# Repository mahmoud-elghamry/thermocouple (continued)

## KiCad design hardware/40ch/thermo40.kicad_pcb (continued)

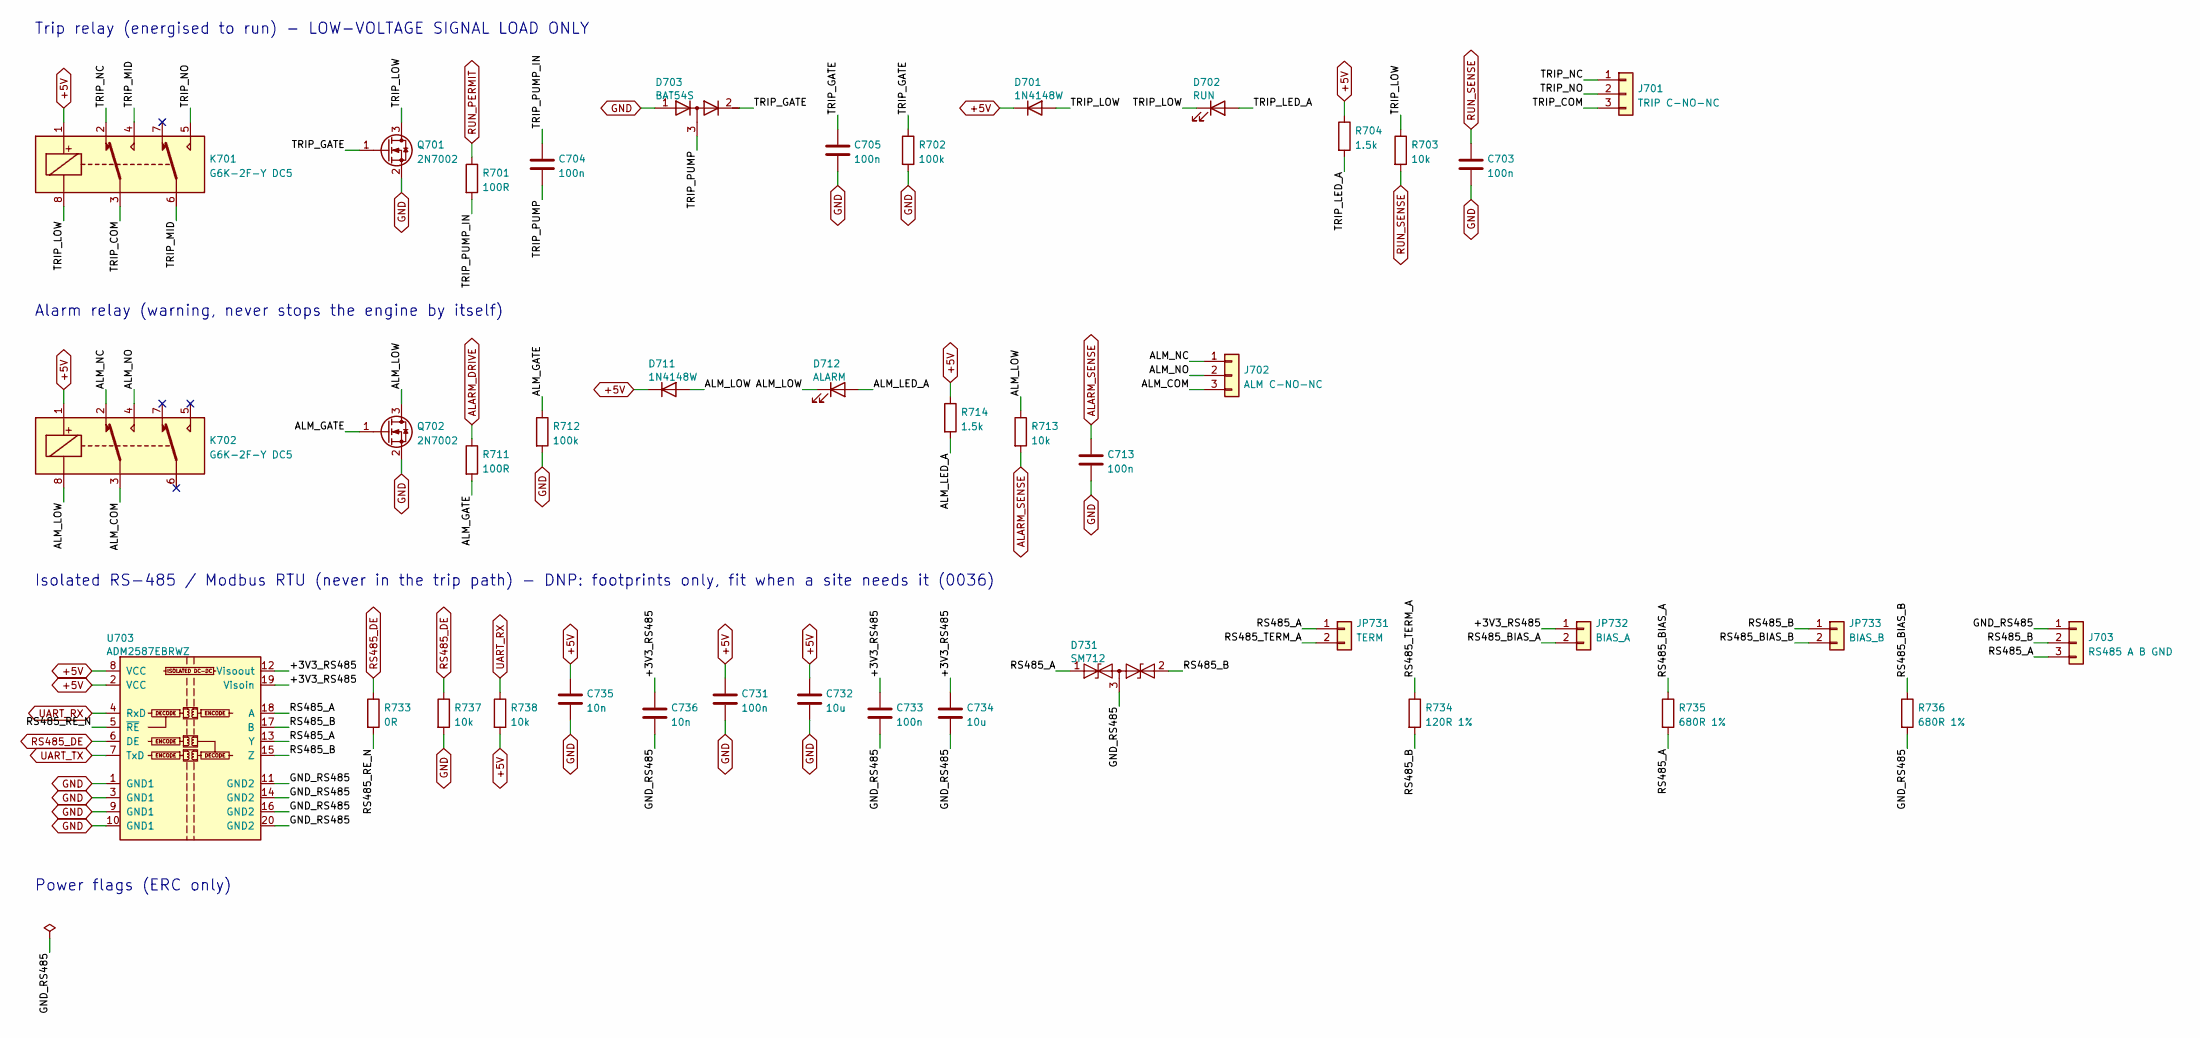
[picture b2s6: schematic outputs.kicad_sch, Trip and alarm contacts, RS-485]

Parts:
C703, C704, C705, C713, C731, C733: 100n; C_0805_2012Metric; MPN CC0805KRX7R9BB104; LCSC C49678
C732, C734: 10u; C_0805_2012Metric; MPN CL21B106KOQNNNE; LCSC C95841
C735, C736: 10n; C_0805_2012Metric; MPN CL21B103KBANNNC; LCSC C1710
D701, D711: 1N4148W; D_SOD-123; MPN 1N4148W-7-F; LCSC C83528
D702: RUN; LED_D3.0mm; MPN 3A4GUD; LCSC C52034646
D703: BAT54S; SOT-23; MPN BAT54S,215; LCSC C47546
D712: ALARM; LED_D3.0mm; MPN 204-10SURD/S530-A3-L; LCSC C99771
D731: SM712; SOT-23; MPN SM712.TCT; LCSC C12067
J701: TRIP C-NO-NC; TerminalBlock_Phoenix_MKDS-1,5-3_1x03_P5.00mm_Horizontal; MPN WJ128V-5.0-3P; LCSC C8270
J702: ALM C-NO-NC; TerminalBlock_Phoenix_MKDS-1,5-3_1x03_P5.00mm_Horizontal; MPN WJ128V-5.0-3P; LCSC C8270
J703: RS485 A B GND; TerminalBlock_Phoenix_MKDS-1,5-3_1x03_P5.00mm_Horizontal; MPN WJ128V-5.0-3P; LCSC C8270
JP731: TERM; PinHeader_1x02_P2.54mm_Vertical; MPN PZ254V-11-02P; LCSC C492401
JP732: BIAS_A; PinHeader_1x02_P2.54mm_Vertical; MPN PZ254V-11-02P; LCSC C492401
JP733: BIAS_B; PinHeader_1x02_P2.54mm_Vertical; MPN PZ254V-11-02P; LCSC C492401
K701, K702: G6K-2F-Y DC5; Relay_DPDT_Omron_G6K-2F-Y; MPN G6K-2F-Y DC5; LCSC C2982926
Q701, Q702: 2N7002; SOT-23; MPN 2N7002; LCSC C8545
R701, R711: 100R; R_0805_2012Metric; MPN 0805W8F1000T5E; LCSC C17408
R702, R712: 100k; R_0805_2012Metric; MPN 0805W8F1003T5E; LCSC C149504
R703, R713, R737, R738: 10k; R_0805_2012Metric; MPN 0805W8F1002T5E; LCSC C17414
R704, R714: 1.5k; R_0805_2012Metric; MPN 0805W8F1501T5E; LCSC C4310
R733: 0R; R_0805_2012Metric; MPN 0805W8F0000T5E; LCSC C17477
R734: 120R 1%; R_0805_2012Metric; MPN 0805W8F1200T5E; LCSC C17437
R735, R736: 680R 1%; R_0805_2012Metric; MPN 0805W8F6800T5E; LCSC C17798
U703: ADM2587EBRWZ; SOIC-20W_7.5x12.8mm_P1.27mm; MPN ADM2587EBRWZ-REEL7; LCSC C12081

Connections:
+5V: C731.1, C732.1, C735.1, D701.1 (K), D711.1 (K), K701.1, K702.1, R704.1, R714.1, R738.2, U703.2 (VCC), U703.8 (VCC); also elsewhere on the board
/OUTPUTS/+3V3_RS485: C733.1, C734.1, C736.1, JP732.1, U703.12 (Visoout), U703.19 (Visoin)
/OUTPUTS/ALM_COM: J702.3, K702.3
/OUTPUTS/ALM_GATE: Q702.1 (G), R711.2, R712.1
/OUTPUTS/ALM_LED_A: D712.2 (A), R714.2
/OUTPUTS/ALM_LOW: D711.2 (A), D712.1 (K), K702.8, Q702.3 (D), R713.1
/OUTPUTS/ALM_NC: J702.1, K702.2
/OUTPUTS/ALM_NO: J702.2, K702.4
/OUTPUTS/GND_RS485: C733.2, C734.2, C736.2, D731.3 (common), J703.1, R736.2, U703.11 (GND2), U703.14 (GND2), U703.16 (GND2), U703.20 (GND2)
/OUTPUTS/RS485_A: D731.1 (A1), J703.3, JP731.1, R735.2, U703.13 (Y), U703.18 (A)
/OUTPUTS/RS485_B: D731.2 (A2), J703.2, JP733.1, R734.2, U703.15 (Z), U703.17 (B)
/OUTPUTS/RS485_BIAS_A: JP732.2, R735.1
/OUTPUTS/RS485_BIAS_B: JP733.2, R736.1
/OUTPUTS/RS485_RE_N: R733.2, U703.5 (~RE)
/OUTPUTS/RS485_TERM_A: JP731.2, R734.1
/OUTPUTS/TRIP_COM: J701.3, K701.3
/OUTPUTS/TRIP_GATE: C705.1, D703.2 (K), Q701.1 (G), R702.1
/OUTPUTS/TRIP_LED_A: D702.2 (A), R704.2
/OUTPUTS/TRIP_LOW: D701.2 (A), D702.1 (K), K701.8, Q701.3 (D), R703.1
/OUTPUTS/TRIP_MID: K701.4, K701.6
/OUTPUTS/TRIP_NC: J701.1, K701.2
/OUTPUTS/TRIP_NO: J701.2, K701.5
/OUTPUTS/TRIP_PUMP: C704.2, D703.3 (common)
/OUTPUTS/TRIP_PUMP_IN: C704.1, R701.2
ALARM_DRIVE: R711.1; also elsewhere on the board
ALARM_SENSE: C713.1, R713.2; also elsewhere on the board
GND: C703.2, C705.2, C713.2, C731.2, C732.2, C735.2, D703.1 (A), Q701.2 (S), Q702.2 (S), R702.2, R712.2, R737.2, U703.1 (GND1), U703.3 (GND1), U703.9 (GND1), U703.10 (GND1); also elsewhere on the board
RS485_DE: R733.1, R737.1, U703.6 (DE); also elsewhere on the board
RUN_PERMIT: R701.1; also elsewhere on the board
RUN_SENSE: C703.1, R703.2; also elsewhere on the board
UART_RX: R738.1, U703.4 (RxD); also elsewhere on the board
UART_TX: U703.7 (TxD); also elsewhere on the board

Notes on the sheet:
Trip relay (energised to run) - LOW-VOLTAGE SIGNAL LOAD ONLY
Alarm relay (warning, never stops the engine by itself)
Isolated RS-485 / Modbus RTU (never in the trip path) - DNP: footprints only, fit when a site needs it (0036)
Power flags (ERC only)

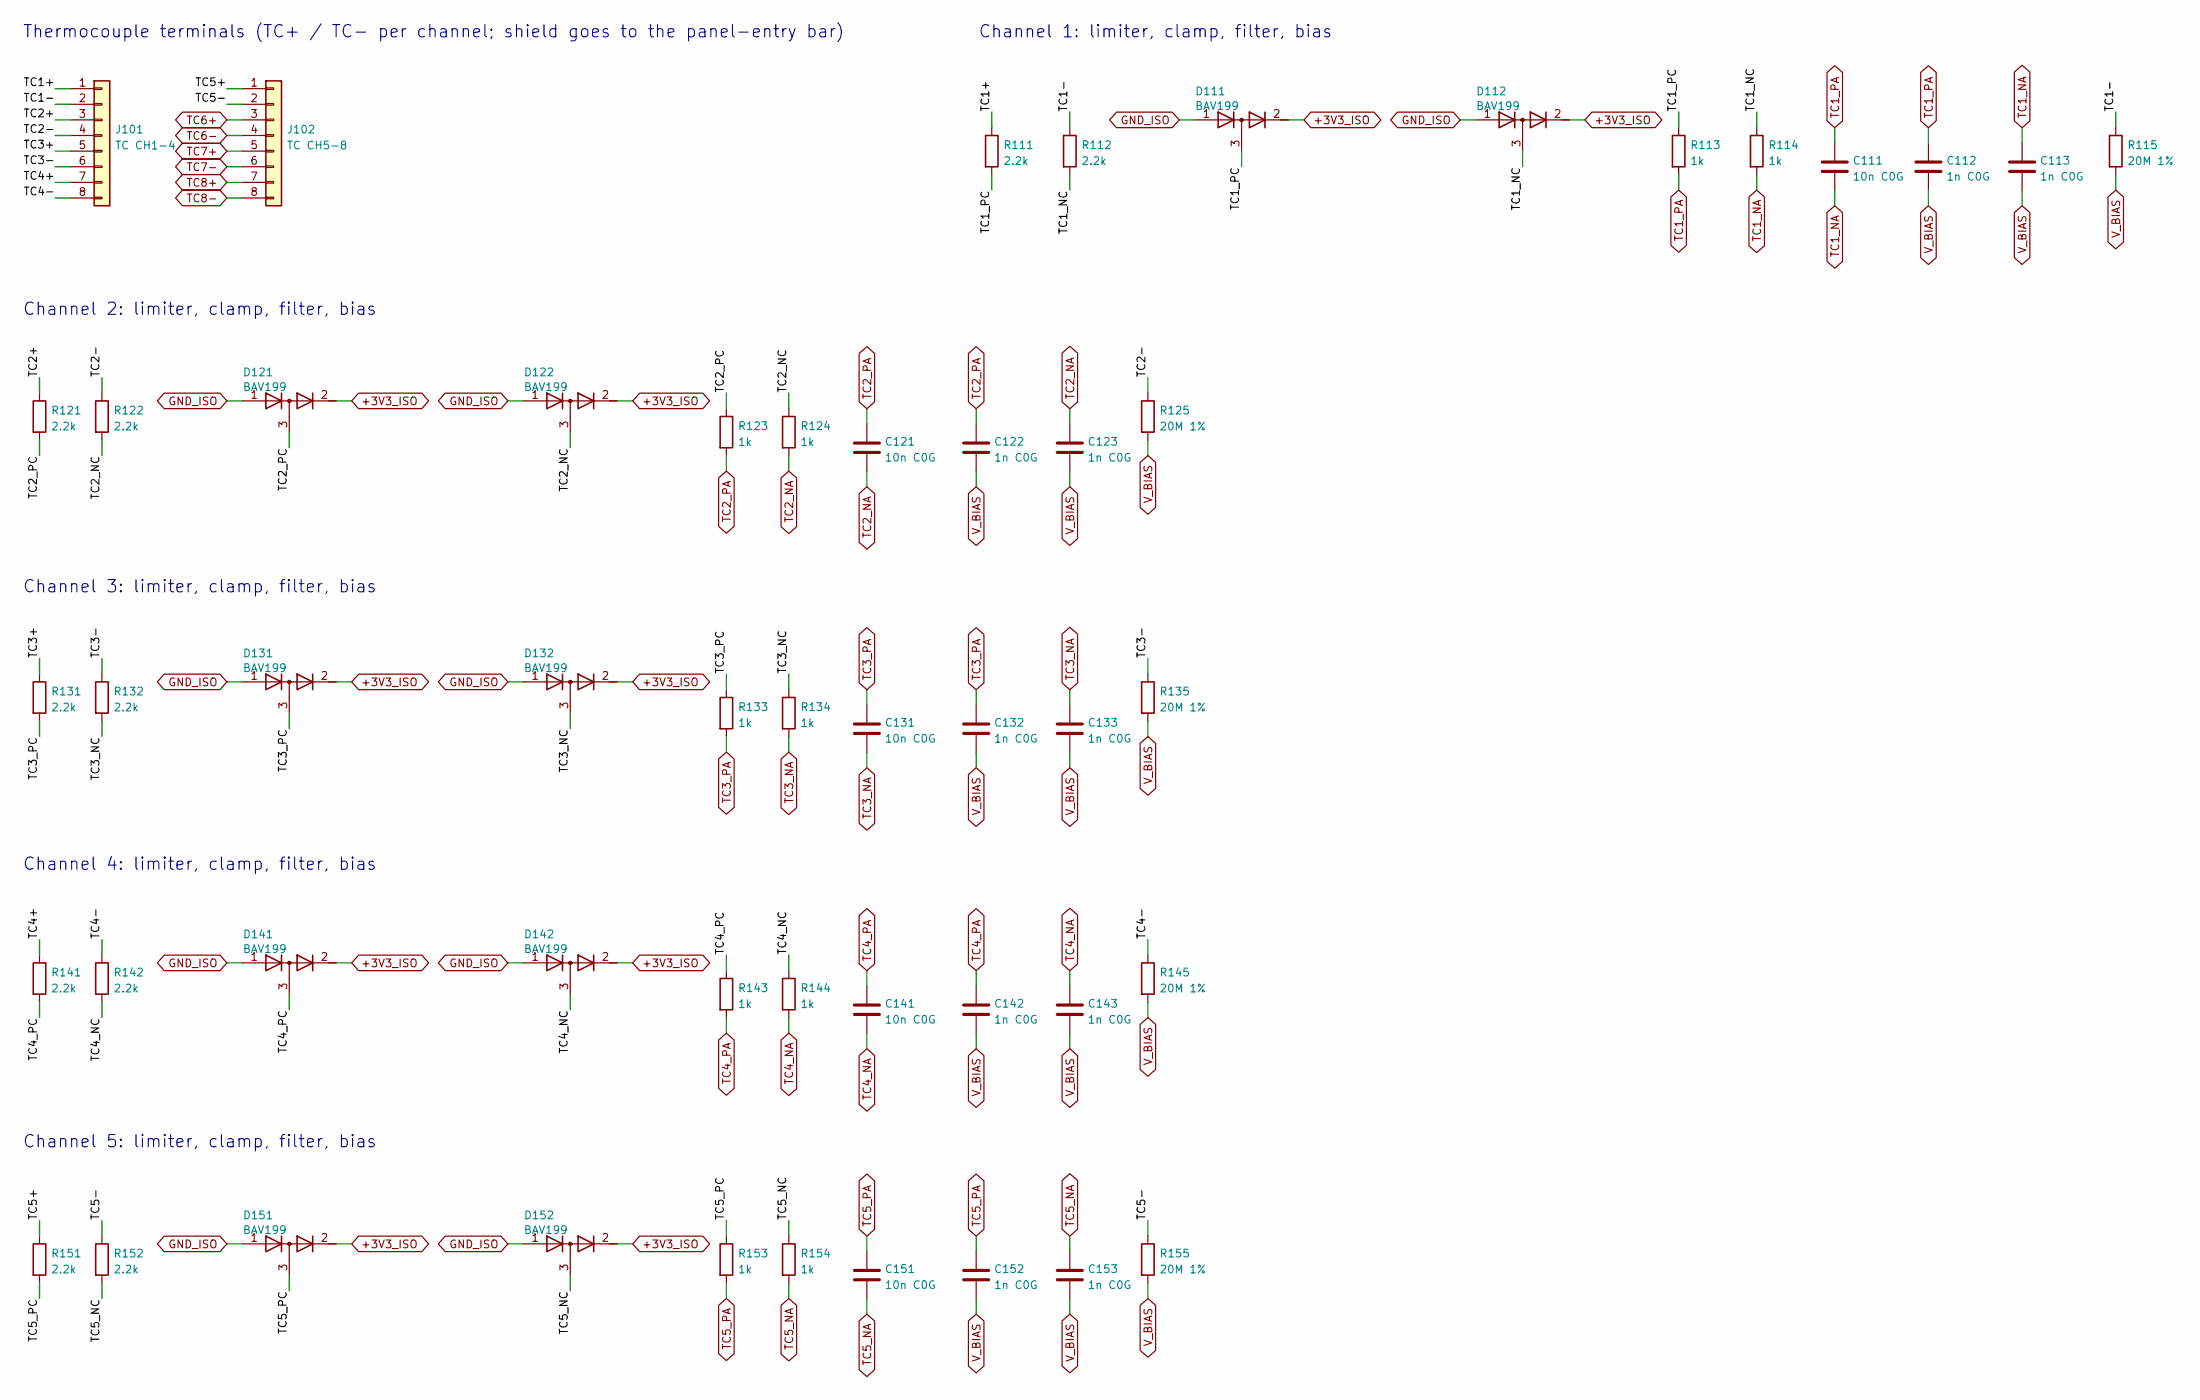
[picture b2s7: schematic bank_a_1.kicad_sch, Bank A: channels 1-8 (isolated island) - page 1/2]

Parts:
C111, C121, C131, C141, C151: 10n C0G; C_0805_2012Metric; MPN GRM2195C1H103JA01D; LCSC C97905
C112, C113, C122, C123, C132, C133, C142, C143, C152, C153: 1n C0G; C_0805_2012Metric; MPN CL21C102JBCNNNC; LCSC C1791
D111, D112, D121, D122, D131, D132, D141, D142, D151, D152: BAV199; SOT-23; MPN BAV199,215; LCSC C40919
J101: TC CH1-4; PhoenixContact_MC_1,5_8-G-3.81_1x08_P3.81mm_Horizontal; MPN WJ15EDGRC-3.81-8P; LCSC C14235
J102: TC CH5-8; PhoenixContact_MC_1,5_8-G-3.81_1x08_P3.81mm_Horizontal; MPN WJ15EDGRC-3.81-8P; LCSC C14235
R111, R112, R121, R122, R131, R132, R141, R142, R151, R152: 2.2k; R_0805_2012Metric; MPN 0805W8F2201T5E; LCSC C17520
R113, R114, R123, R124, R133, R134, R143, R144, R153, R154: 1k; R_0805_2012Metric; MPN 0805W8F1001T5E; LCSC C17513
R115, R125, R135, R145, R155: 20M 1%; R_1206_3216Metric; MPN FRG1206F2005TS; LCSC C3000606

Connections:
+3V3_ISO: D111.2 (K), D112.2 (K), D121.2 (K), D122.2 (K), D131.2 (K), D132.2 (K), D141.2 (K), D142.2 (K), D151.2 (K), D152.2 (K); also elsewhere on the board
/BANK_A_1/TC1+: J101.1, R111.1
/BANK_A_1/TC1-: J101.2, R112.1, R115.1
/BANK_A_1/TC1_NC: D112.3 (common), R112.2, R114.1
/BANK_A_1/TC1_PC: D111.3 (common), R111.2, R113.1
/BANK_A_1/TC2+: J101.3, R121.1
/BANK_A_1/TC2-: J101.4, R122.1, R125.1
/BANK_A_1/TC2_NC: D122.3 (common), R122.2, R124.1
/BANK_A_1/TC2_PC: D121.3 (common), R121.2, R123.1
/BANK_A_1/TC3+: J101.5, R131.1
/BANK_A_1/TC3-: J101.6, R132.1, R135.1
/BANK_A_1/TC3_NC: D132.3 (common), R132.2, R134.1
/BANK_A_1/TC3_PC: D131.3 (common), R131.2, R133.1
/BANK_A_1/TC4+: J101.7, R141.1
/BANK_A_1/TC4-: J101.8, R142.1, R145.1
/BANK_A_1/TC4_NC: D142.3 (common), R142.2, R144.1
/BANK_A_1/TC4_PC: D141.3 (common), R141.2, R143.1
/BANK_A_1/TC5+: J102.1, R151.1
/BANK_A_1/TC5-: J102.2, R152.1, R155.1
/BANK_A_1/TC5_NC: D152.3 (common), R152.2, R154.1
/BANK_A_1/TC5_PC: D151.3 (common), R151.2, R153.1
GND_ISO: D111.1 (A), D112.1 (A), D121.1 (A), D122.1 (A), D131.1 (A), D132.1 (A), D141.1 (A), D142.1 (A), D151.1 (A), D152.1 (A); also elsewhere on the board
TC1_NA: C111.2, C113.1, R114.2; also elsewhere on the board
TC1_PA: C111.1, C112.1, R113.2; also elsewhere on the board
TC2_NA: C121.2, C123.1, R124.2; also elsewhere on the board
TC2_PA: C121.1, C122.1, R123.2; also elsewhere on the board
TC3_NA: C131.2, C133.1, R134.2; also elsewhere on the board
TC3_PA: C131.1, C132.1, R133.2; also elsewhere on the board
TC4_NA: C141.2, C143.1, R144.2; also elsewhere on the board
TC4_PA: C141.1, C142.1, R143.2; also elsewhere on the board
TC5_NA: C151.2, C153.1, R154.2; also elsewhere on the board
TC5_PA: C151.1, C152.1, R153.2; also elsewhere on the board
TC6+: J102.3; also elsewhere on the board
TC6-: J102.4; also elsewhere on the board
TC7+: J102.5; also elsewhere on the board
TC7-: J102.6; also elsewhere on the board
TC8+: J102.7; also elsewhere on the board
TC8-: J102.8; also elsewhere on the board
V_BIAS: C112.2, C113.2, C122.2, C123.2, C132.2, C133.2, C142.2, C143.2, C152.2, C153.2, R115.2, R125.2, R135.2, R145.2, R155.2; also elsewhere on the board

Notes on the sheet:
Thermocouple terminals (TC+ / TC- per channel; shield goes to the panel-entry bar)
Channel 1: limiter, clamp, filter, bias
Channel 2: limiter, clamp, filter, bias
Channel 3: limiter, clamp, filter, bias
Channel 4: limiter, clamp, filter, bias
Channel 5: limiter, clamp, filter, bias

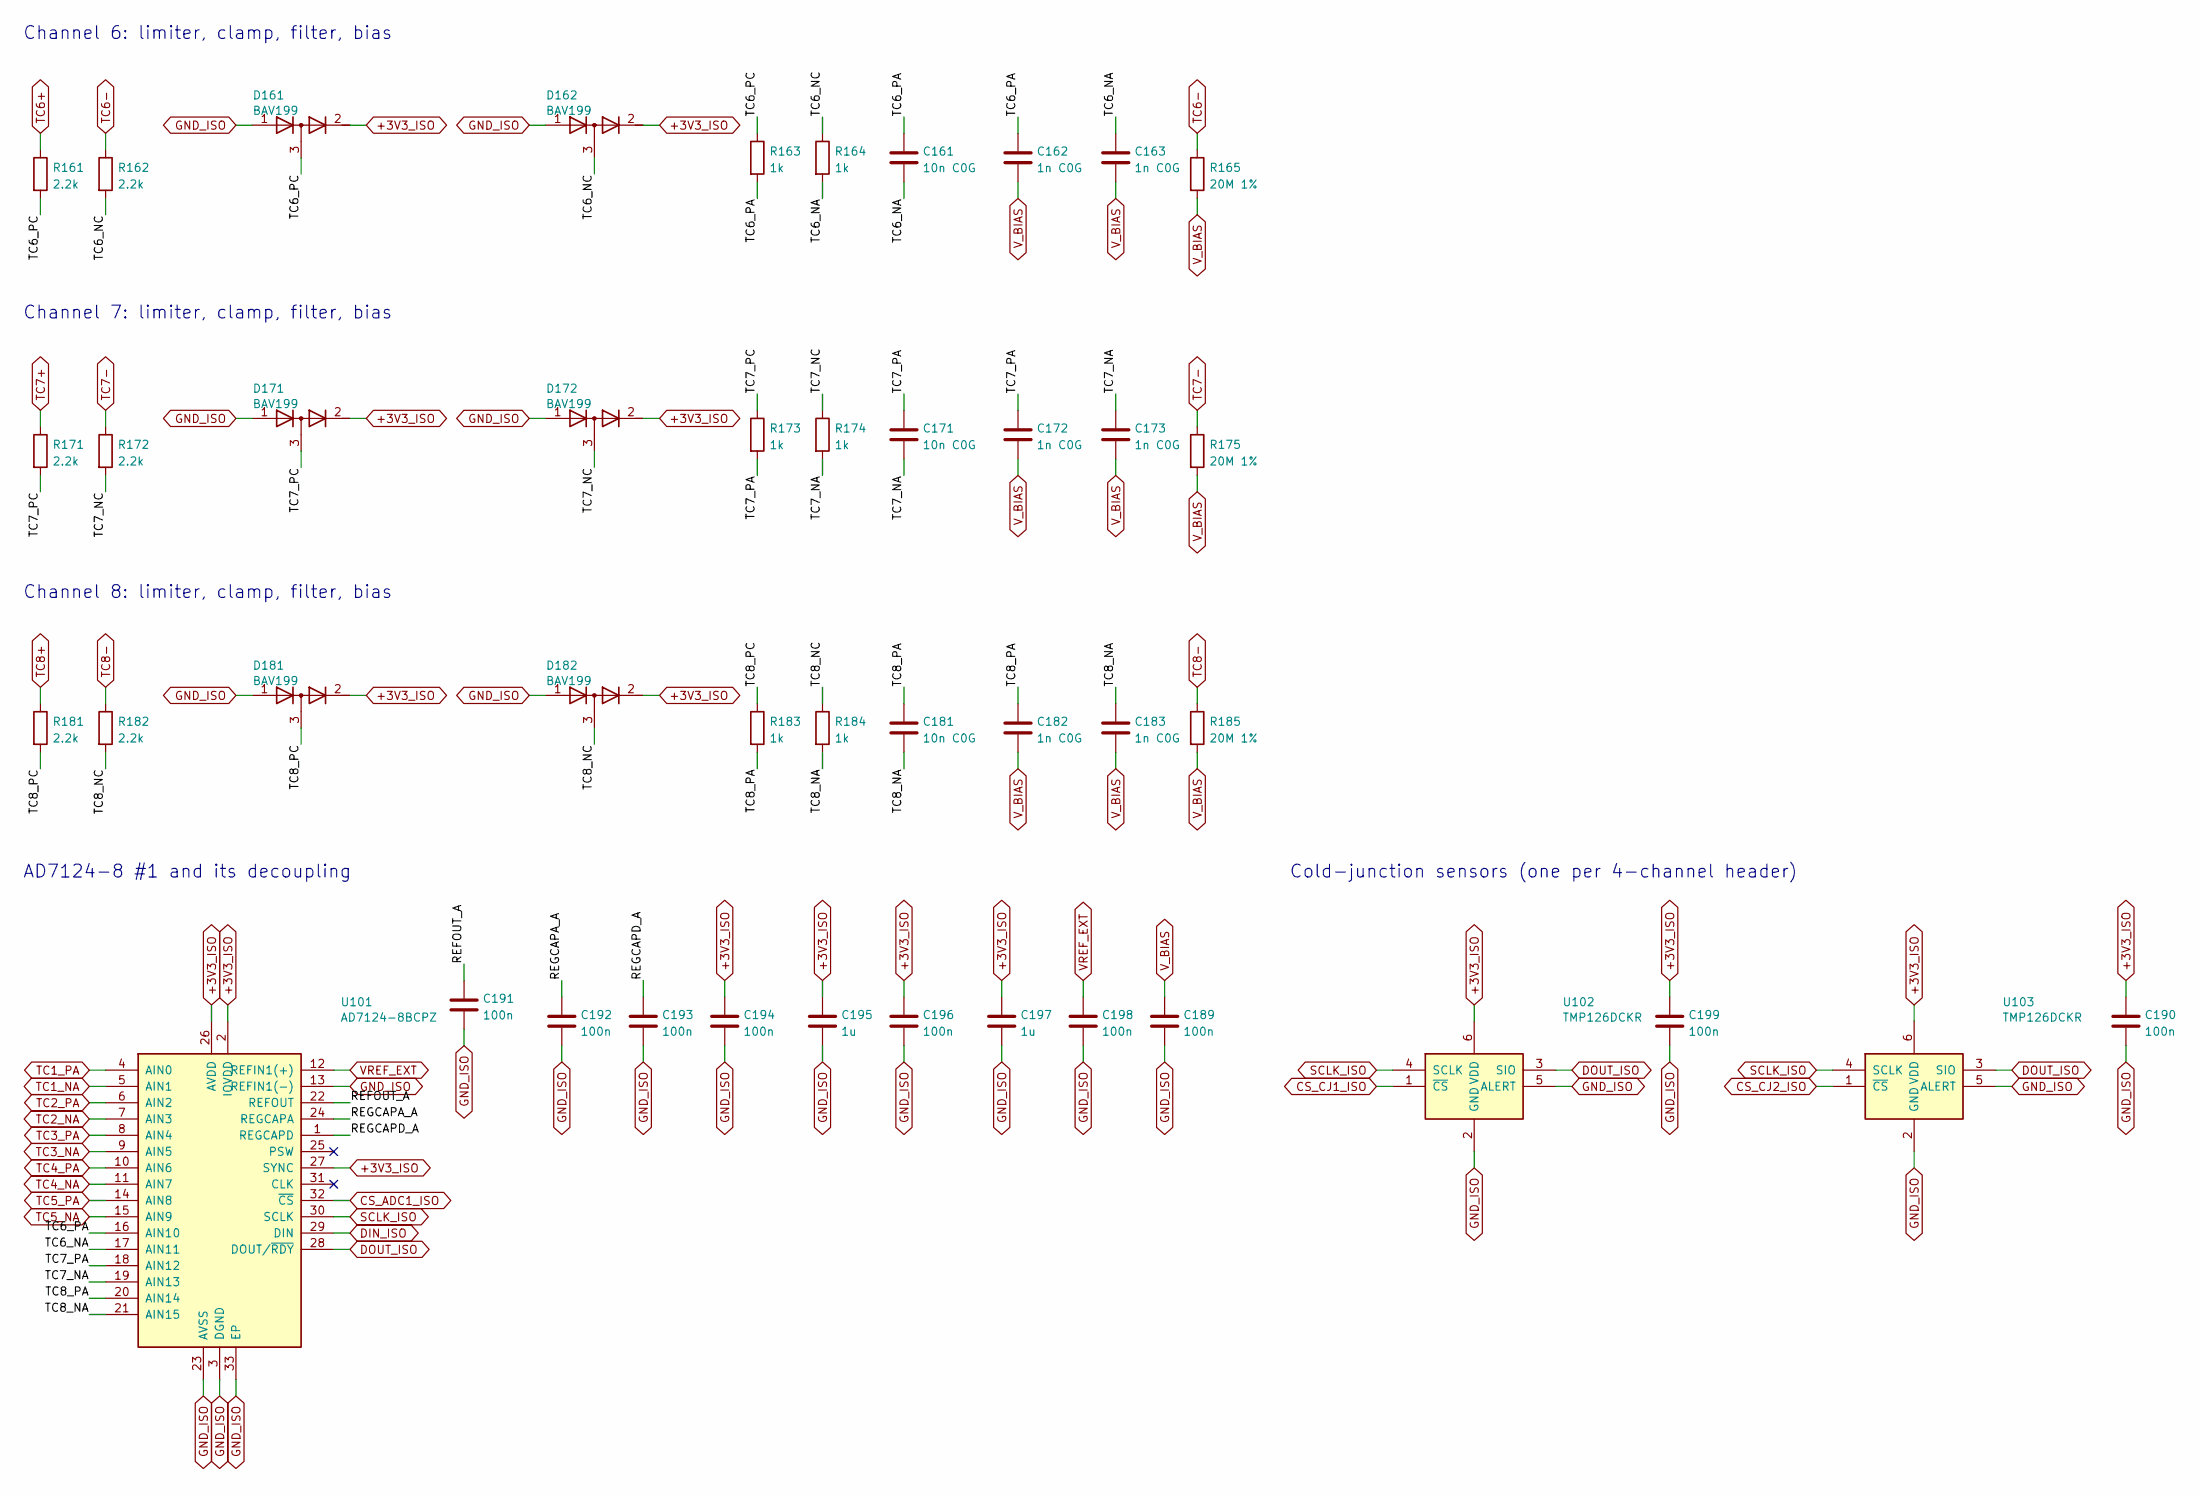
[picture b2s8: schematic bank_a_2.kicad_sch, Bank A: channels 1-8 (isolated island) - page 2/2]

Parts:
C161, C171, C181: 10n C0G; C_0805_2012Metric; MPN GRM2195C1H103JA01D; LCSC C97905
C162, C163, C172, C173, C182, C183: 1n C0G; C_0805_2012Metric; MPN CL21C102JBCNNNC; LCSC C1791
C189, C190, C191, C192, C193, C194, C196, C198, C199: 100n; C_0805_2012Metric; MPN CC0805KRX7R9BB104; LCSC C49678
C195, C197: 1u; C_0805_2012Metric; MPN CL21B105KBFNNNE; LCSC C28323
D161, D162, D171, D172, D181, D182: BAV199; SOT-23; MPN BAV199,215; LCSC C40919
R161, R162, R171, R172, R181, R182: 2.2k; R_0805_2012Metric; MPN 0805W8F2201T5E; LCSC C17520
R163, R164, R173, R174, R183, R184: 1k; R_0805_2012Metric; MPN 0805W8F1001T5E; LCSC C17513
R165, R175, R185: 20M 1%; R_1206_3216Metric; MPN FRG1206F2005TS; LCSC C3000606
U101: AD7124-8BCPZ; LFCSP-32-1EP_5x5mm_P0.5mm_EP3.6x3.6mm; MPN AD7124-8BCPZ; LCSC C97314
U102, U103: TMP126DCKR; SOT-363_SC-70-6; MPN TMP126DCKR; LCSC C5219998

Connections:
+3V3_ISO: C190.1, C194.1, C195.1, C196.1, C197.1, C199.1, D161.2 (K), D162.2 (K), D171.2 (K), D172.2 (K), D181.2 (K), D182.2 (K), U101.2 (IOVDD), U101.26 (AVDD), U101.27 (SYNC), U102.6 (VDD), U103.6 (VDD); also elsewhere on the board
/BANK_A_2/REFOUT_A: C191.1, U101.22 (REFOUT)
/BANK_A_2/REGCAPA_A: C192.1, U101.24 (REGCAPA)
/BANK_A_2/REGCAPD_A: C193.1, U101.1 (REGCAPD)
/BANK_A_2/TC6_NA: C161.2, C163.1, R164.2, U101.17 (AIN11)
/BANK_A_2/TC6_NC: D162.3 (common), R162.2, R164.1
/BANK_A_2/TC6_PA: C161.1, C162.1, R163.2, U101.16 (AIN10)
/BANK_A_2/TC6_PC: D161.3 (common), R161.2, R163.1
/BANK_A_2/TC7_NA: C171.2, C173.1, R174.2, U101.19 (AIN13)
/BANK_A_2/TC7_NC: D172.3 (common), R172.2, R174.1
/BANK_A_2/TC7_PA: C171.1, C172.1, R173.2, U101.18 (AIN12)
/BANK_A_2/TC7_PC: D171.3 (common), R171.2, R173.1
/BANK_A_2/TC8_NA: C181.2, C183.1, R184.2, U101.21 (AIN15)
/BANK_A_2/TC8_NC: D182.3 (common), R182.2, R184.1
/BANK_A_2/TC8_PA: C181.1, C182.1, R183.2, U101.20 (AIN14)
/BANK_A_2/TC8_PC: D181.3 (common), R181.2, R183.1
CS_ADC1_ISO: U101.32 (~CS); also elsewhere on the board
CS_CJ1_ISO: U102.1 (~CS); also elsewhere on the board
CS_CJ2_ISO: U103.1 (~CS); also elsewhere on the board
DIN_ISO: U101.29 (DIN); also elsewhere on the board
DOUT_ISO: U101.28 (DOUT/~RDY), U102.3 (SIO), U103.3 (SIO); also elsewhere on the board
GND_ISO: C189.2, C190.2, C191.2, C192.2, C193.2, C194.2, C195.2, C196.2, C197.2, C198.2, C199.2, D161.1 (A), D162.1 (A), D171.1 (A), D172.1 (A), D181.1 (A), D182.1 (A), U101.3 (DGND), U101.13 (REFIN1(-)), U101.23 (AVSS), U101.33 (EP), U102.2 (GND), U102.5 (ALERT), U103.2 (GND), U103.5 (ALERT); also elsewhere on the board
SCLK_ISO: U101.30 (SCLK), U102.4 (SCLK), U103.4 (SCLK); also elsewhere on the board
TC1_NA: U101.5 (AIN1); also elsewhere on the board
TC1_PA: U101.4 (AIN0); also elsewhere on the board
TC2_NA: U101.7 (AIN3); also elsewhere on the board
TC2_PA: U101.6 (AIN2); also elsewhere on the board
TC3_NA: U101.9 (AIN5); also elsewhere on the board
TC3_PA: U101.8 (AIN4); also elsewhere on the board
TC4_NA: U101.11 (AIN7); also elsewhere on the board
TC4_PA: U101.10 (AIN6); also elsewhere on the board
TC5_NA: U101.15 (AIN9); also elsewhere on the board
TC5_PA: U101.14 (AIN8); also elsewhere on the board
TC6+: R161.1; also elsewhere on the board
TC6-: R162.1, R165.1; also elsewhere on the board
TC7+: R171.1; also elsewhere on the board
TC7-: R172.1, R175.1; also elsewhere on the board
TC8+: R181.1; also elsewhere on the board
TC8-: R182.1, R185.1; also elsewhere on the board
VREF_EXT: C198.1, U101.12 (REFIN1(+)); also elsewhere on the board
V_BIAS: C162.2, C163.2, C172.2, C173.2, C182.2, C183.2, C189.1, R165.2, R175.2, R185.2; also elsewhere on the board

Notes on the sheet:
Channel 6: limiter, clamp, filter, bias
Channel 7: limiter, clamp, filter, bias
Channel 8: limiter, clamp, filter, bias
AD7124-8 #1 and its decoupling
Cold-junction sensors (one per 4-channel header)

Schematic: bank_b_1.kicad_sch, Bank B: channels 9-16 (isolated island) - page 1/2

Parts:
C211, C221, C231, C241, C251: 10n C0G; C_0805_2012Metric; MPN GRM2195C1H103JA01D; LCSC C97905
C212, C213, C222, C223, C232, C233, C242, C243, C252, C253: 1n C0G; C_0805_2012Metric; MPN CL21C102JBCNNNC; LCSC C1791
D211, D212, D221, D222, D231, D232, D241, D242, D251, D252: BAV199; SOT-23; MPN BAV199,215; LCSC C40919
J201: TC CH9-12; PhoenixContact_MC_1,5_8-G-3.81_1x08_P3.81mm_Horizontal; MPN WJ15EDGRC-3.81-8P; LCSC C14235
J202: TC CH13-16; PhoenixContact_MC_1,5_8-G-3.81_1x08_P3.81mm_Horizontal; MPN WJ15EDGRC-3.81-8P; LCSC C14235
R211, R212, R221, R222, R231, R232, R241, R242, R251, R252: 2.2k; R_0805_2012Metric; MPN 0805W8F2201T5E; LCSC C17520
R213, R214, R223, R224, R233, R234, R243, R244, R253, R254: 1k; R_0805_2012Metric; MPN 0805W8F1001T5E; LCSC C17513
R215, R225, R235, R245, R255: 20M 1%; R_1206_3216Metric; MPN FRG1206F2005TS; LCSC C3000606

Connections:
+3V3_ISO: D211.2 (K), D212.2 (K), D221.2 (K), D222.2 (K), D231.2 (K), D232.2 (K), D241.2 (K), D242.2 (K), D251.2 (K), D252.2 (K); also elsewhere on the board
/BANK_B_1/TC9+: J201.1, R211.1
/BANK_B_1/TC9-: J201.2, R212.1, R215.1
/BANK_B_1/TC9_NC: D212.3 (common), R212.2, R214.1
/BANK_B_1/TC9_PC: D211.3 (common), R211.2, R213.1
/BANK_B_1/TC10+: J201.3, R221.1
/BANK_B_1/TC10-: J201.4, R222.1, R225.1
/BANK_B_1/TC10_NC: D222.3 (common), R222.2, R224.1
/BANK_B_1/TC10_PC: D221.3 (common), R221.2, R223.1
/BANK_B_1/TC11+: J201.5, R231.1
/BANK_B_1/TC11-: J201.6, R232.1, R235.1
/BANK_B_1/TC11_NC: D232.3 (common), R232.2, R234.1
/BANK_B_1/TC11_PC: D231.3 (common), R231.2, R233.1
/BANK_B_1/TC12+: J201.7, R241.1
/BANK_B_1/TC12-: J201.8, R242.1, R245.1
/BANK_B_1/TC12_NC: D242.3 (common), R242.2, R244.1
/BANK_B_1/TC12_PC: D241.3 (common), R241.2, R243.1
/BANK_B_1/TC13+: J202.1, R251.1
/BANK_B_1/TC13-: J202.2, R252.1, R255.1
/BANK_B_1/TC13_NC: D252.3 (common), R252.2, R254.1
/BANK_B_1/TC13_PC: D251.3 (common), R251.2, R253.1
GND_ISO: D211.1 (A), D212.1 (A), D221.1 (A), D222.1 (A), D231.1 (A), D232.1 (A), D241.1 (A), D242.1 (A), D251.1 (A), D252.1 (A); also elsewhere on the board
TC9_NA: C211.2, C213.1, R214.2; also elsewhere on the board
TC9_PA: C211.1, C212.1, R213.2; also elsewhere on the board
TC10_NA: C221.2, C223.1, R224.2; also elsewhere on the board
TC10_PA: C221.1, C222.1, R223.2; also elsewhere on the board
TC11_NA: C231.2, C233.1, R234.2; also elsewhere on the board
TC11_PA: C231.1, C232.1, R233.2; also elsewhere on the board
TC12_NA: C241.2, C243.1, R244.2; also elsewhere on the board
TC12_PA: C241.1, C242.1, R243.2; also elsewhere on the board
TC13_NA: C251.2, C253.1, R254.2; also elsewhere on the board
TC13_PA: C251.1, C252.1, R253.2; also elsewhere on the board
TC14+: J202.3; also elsewhere on the board
TC14-: J202.4; also elsewhere on the board
TC15+: J202.5; also elsewhere on the board
TC15-: J202.6; also elsewhere on the board
TC16+: J202.7; also elsewhere on the board
TC16-: J202.8; also elsewhere on the board
V_BIAS: C212.2, C213.2, C222.2, C223.2, C232.2, C233.2, C242.2, C243.2, C252.2, C253.2, R215.2, R225.2, R235.2, R245.2, R255.2; also elsewhere on the board

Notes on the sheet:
Thermocouple terminals (TC+ / TC- per channel; shield goes to the panel-entry bar)
Channel 9: limiter, clamp, filter, bias
Channel 10: limiter, clamp, filter, bias
Channel 11: limiter, clamp, filter, bias
Channel 12: limiter, clamp, filter, bias
Channel 13: limiter, clamp, filter, bias

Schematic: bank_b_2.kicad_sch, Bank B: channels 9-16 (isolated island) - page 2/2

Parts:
C261, C271, C281: 10n C0G; C_0805_2012Metric; MPN GRM2195C1H103JA01D; LCSC C97905
C262, C263, C272, C273, C282, C283: 1n C0G; C_0805_2012Metric; MPN CL21C102JBCNNNC; LCSC C1791
C289, C290, C291, C292, C293, C294, C296, C298, C299: 100n; C_0805_2012Metric; MPN CC0805KRX7R9BB104; LCSC C49678
C295, C297: 1u; C_0805_2012Metric; MPN CL21B105KBFNNNE; LCSC C28323
D261, D262, D271, D272, D281, D282: BAV199; SOT-23; MPN BAV199,215; LCSC C40919
R261, R262, R271, R272, R281, R282: 2.2k; R_0805_2012Metric; MPN 0805W8F2201T5E; LCSC C17520
R263, R264, R273, R274, R283, R284: 1k; R_0805_2012Metric; MPN 0805W8F1001T5E; LCSC C17513
R265, R275, R285: 20M 1%; R_1206_3216Metric; MPN FRG1206F2005TS; LCSC C3000606
U201: AD7124-8BCPZ; LFCSP-32-1EP_5x5mm_P0.5mm_EP3.6x3.6mm; MPN AD7124-8BCPZ; LCSC C97314
U202, U203: TMP126DCKR; SOT-363_SC-70-6; MPN TMP126DCKR; LCSC C5219998

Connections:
+3V3_ISO: C290.1, C294.1, C295.1, C296.1, C297.1, C299.1, D261.2 (K), D262.2 (K), D271.2 (K), D272.2 (K), D281.2 (K), D282.2 (K), U201.2 (IOVDD), U201.26 (AVDD), U201.27 (SYNC), U202.6 (VDD), U203.6 (VDD); also elsewhere on the board
/BANK_B_2/REFOUT_B: C291.1, U201.22 (REFOUT)
/BANK_B_2/REGCAPA_B: C292.1, U201.24 (REGCAPA)
/BANK_B_2/REGCAPD_B: C293.1, U201.1 (REGCAPD)
/BANK_B_2/TC14_NA: C261.2, C263.1, R264.2, U201.17 (AIN11)
/BANK_B_2/TC14_NC: D262.3 (common), R262.2, R264.1
/BANK_B_2/TC14_PA: C261.1, C262.1, R263.2, U201.16 (AIN10)
/BANK_B_2/TC14_PC: D261.3 (common), R261.2, R263.1
/BANK_B_2/TC15_NA: C271.2, C273.1, R274.2, U201.19 (AIN13)
/BANK_B_2/TC15_NC: D272.3 (common), R272.2, R274.1
/BANK_B_2/TC15_PA: C271.1, C272.1, R273.2, U201.18 (AIN12)
/BANK_B_2/TC15_PC: D271.3 (common), R271.2, R273.1
/BANK_B_2/TC16_NA: C281.2, C283.1, R284.2, U201.21 (AIN15)
/BANK_B_2/TC16_NC: D282.3 (common), R282.2, R284.1
/BANK_B_2/TC16_PA: C281.1, C282.1, R283.2, U201.20 (AIN14)
/BANK_B_2/TC16_PC: D281.3 (common), R281.2, R283.1
CS_ADC2_ISO: U201.32 (~CS); also elsewhere on the board
CS_CJ3_ISO: U202.1 (~CS); also elsewhere on the board
CS_CJ4_ISO: U203.1 (~CS); also elsewhere on the board
DIN_ISO: U201.29 (DIN); also elsewhere on the board
DOUT_ISO: U201.28 (DOUT/~RDY), U202.3 (SIO), U203.3 (SIO); also elsewhere on the board
GND_ISO: C289.2, C290.2, C291.2, C292.2, C293.2, C294.2, C295.2, C296.2, C297.2, C298.2, C299.2, D261.1 (A), D262.1 (A), D271.1 (A), D272.1 (A), D281.1 (A), D282.1 (A), U201.3 (DGND), U201.13 (REFIN1(-)), U201.23 (AVSS), U201.33 (EP), U202.2 (GND), U202.5 (ALERT), U203.2 (GND), U203.5 (ALERT); also elsewhere on the board
SCLK_ISO: U201.30 (SCLK), U202.4 (SCLK), U203.4 (SCLK); also elsewhere on the board
TC9_NA: U201.5 (AIN1); also elsewhere on the board
TC9_PA: U201.4 (AIN0); also elsewhere on the board
TC10_NA: U201.7 (AIN3); also elsewhere on the board
TC10_PA: U201.6 (AIN2); also elsewhere on the board
TC11_NA: U201.9 (AIN5); also elsewhere on the board
TC11_PA: U201.8 (AIN4); also elsewhere on the board
TC12_NA: U201.11 (AIN7); also elsewhere on the board
TC12_PA: U201.10 (AIN6); also elsewhere on the board
TC13_NA: U201.15 (AIN9); also elsewhere on the board
TC13_PA: U201.14 (AIN8); also elsewhere on the board
TC14+: R261.1; also elsewhere on the board
TC14-: R262.1, R265.1; also elsewhere on the board
TC15+: R271.1; also elsewhere on the board
TC15-: R272.1, R275.1; also elsewhere on the board
TC16+: R281.1; also elsewhere on the board
TC16-: R282.1, R285.1; also elsewhere on the board
VREF_EXT: C298.1, U201.12 (REFIN1(+)); also elsewhere on the board
V_BIAS: C262.2, C263.2, C272.2, C273.2, C282.2, C283.2, C289.1, R265.2, R275.2, R285.2; also elsewhere on the board

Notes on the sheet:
Channel 14: limiter, clamp, filter, bias
Channel 15: limiter, clamp, filter, bias
Channel 16: limiter, clamp, filter, bias
AD7124-8 #2 and its decoupling
Cold-junction sensors (one per 4-channel header)

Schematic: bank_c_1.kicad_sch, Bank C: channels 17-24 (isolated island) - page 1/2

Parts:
C311, C321, C331, C341, C351: 10n C0G; C_0805_2012Metric; MPN GRM2195C1H103JA01D; LCSC C97905
C312, C313, C322, C323, C332, C333, C342, C343, C352, C353: 1n C0G; C_0805_2012Metric; MPN CL21C102JBCNNNC; LCSC C1791
D311, D312, D321, D322, D331, D332, D341, D342, D351, D352: BAV199; SOT-23; MPN BAV199,215; LCSC C40919
J301: TC CH17-20; PhoenixContact_MC_1,5_8-G-3.81_1x08_P3.81mm_Horizontal; MPN WJ15EDGRC-3.81-8P; LCSC C14235
J302: TC CH21-24; PhoenixContact_MC_1,5_8-G-3.81_1x08_P3.81mm_Horizontal; MPN WJ15EDGRC-3.81-8P; LCSC C14235
R311, R312, R321, R322, R331, R332, R341, R342, R351, R352: 2.2k; R_0805_2012Metric; MPN 0805W8F2201T5E; LCSC C17520
R313, R314, R323, R324, R333, R334, R343, R344, R353, R354: 1k; R_0805_2012Metric; MPN 0805W8F1001T5E; LCSC C17513
R315, R325, R335, R345, R355: 20M 1%; R_1206_3216Metric; MPN FRG1206F2005TS; LCSC C3000606

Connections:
+3V3_ISO: D311.2 (K), D312.2 (K), D321.2 (K), D322.2 (K), D331.2 (K), D332.2 (K), D341.2 (K), D342.2 (K), D351.2 (K), D352.2 (K); also elsewhere on the board
/BANK_C_1/TC17+: J301.1, R311.1
/BANK_C_1/TC17-: J301.2, R312.1, R315.1
/BANK_C_1/TC17_NC: D312.3 (common), R312.2, R314.1
/BANK_C_1/TC17_PC: D311.3 (common), R311.2, R313.1
/BANK_C_1/TC18+: J301.3, R321.1
/BANK_C_1/TC18-: J301.4, R322.1, R325.1
/BANK_C_1/TC18_NC: D322.3 (common), R322.2, R324.1
/BANK_C_1/TC18_PC: D321.3 (common), R321.2, R323.1
/BANK_C_1/TC19+: J301.5, R331.1
/BANK_C_1/TC19-: J301.6, R332.1, R335.1
/BANK_C_1/TC19_NC: D332.3 (common), R332.2, R334.1
/BANK_C_1/TC19_PC: D331.3 (common), R331.2, R333.1
/BANK_C_1/TC20+: J301.7, R341.1
/BANK_C_1/TC20-: J301.8, R342.1, R345.1
/BANK_C_1/TC20_NC: D342.3 (common), R342.2, R344.1
/BANK_C_1/TC20_PC: D341.3 (common), R341.2, R343.1
/BANK_C_1/TC21+: J302.1, R351.1
/BANK_C_1/TC21-: J302.2, R352.1, R355.1
/BANK_C_1/TC21_NC: D352.3 (common), R352.2, R354.1
/BANK_C_1/TC21_PC: D351.3 (common), R351.2, R353.1
GND_ISO: D311.1 (A), D312.1 (A), D321.1 (A), D322.1 (A), D331.1 (A), D332.1 (A), D341.1 (A), D342.1 (A), D351.1 (A), D352.1 (A); also elsewhere on the board
TC17_NA: C311.2, C313.1, R314.2; also elsewhere on the board
TC17_PA: C311.1, C312.1, R313.2; also elsewhere on the board
TC18_NA: C321.2, C323.1, R324.2; also elsewhere on the board
TC18_PA: C321.1, C322.1, R323.2; also elsewhere on the board
TC19_NA: C331.2, C333.1, R334.2; also elsewhere on the board
TC19_PA: C331.1, C332.1, R333.2; also elsewhere on the board
TC20_NA: C341.2, C343.1, R344.2; also elsewhere on the board
TC20_PA: C341.1, C342.1, R343.2; also elsewhere on the board
TC21_NA: C351.2, C353.1, R354.2; also elsewhere on the board
TC21_PA: C351.1, C352.1, R353.2; also elsewhere on the board
TC22+: J302.3; also elsewhere on the board
TC22-: J302.4; also elsewhere on the board
TC23+: J302.5; also elsewhere on the board
TC23-: J302.6; also elsewhere on the board
TC24+: J302.7; also elsewhere on the board
TC24-: J302.8; also elsewhere on the board
V_BIAS: C312.2, C313.2, C322.2, C323.2, C332.2, C333.2, C342.2, C343.2, C352.2, C353.2, R315.2, R325.2, R335.2, R345.2, R355.2; also elsewhere on the board

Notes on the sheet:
Thermocouple terminals (TC+ / TC- per channel; shield goes to the panel-entry bar)
Channel 17: limiter, clamp, filter, bias
Channel 18: limiter, clamp, filter, bias
Channel 19: limiter, clamp, filter, bias
Channel 20: limiter, clamp, filter, bias
Channel 21: limiter, clamp, filter, bias
